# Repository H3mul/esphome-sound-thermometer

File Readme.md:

# Sound Thermometer

A quick ESPHome project that illuminates an addressable LED strip based on sound levels detected by a microphone module.

## Features

- Custom LED effect that lerps between two colors based on sound level
- Configurable sound sensitivity and LED colors via ESPHome webui
- Support for USB C and A power source capability detection
- Safety kill switch via a mosfet to disable the LED load if the power source doesn't support enough current
- Pins for power switch

## Media

https://github.com/user-attachments/assets/a23c17ae-ab65-41b6-94d6-0d3440485dc3

## Hardware Design

### Schematic Diagram

### PCB Layout

## Components

- Microcontroller (ESP32-C3 Super Mini)
- WS2812B LED strip
- Microphone module with analog out (e.g., MAX9814)
- AMS1117-3.3 Voltage Regulator for clean mic module power
- P-Channel MOSFET for power control (AO3401)
- P2N2222A NPN transistor for mosfet driving
- USB C 8-pin breakout board with 5.1k resistors for CC pins (designating the device as a power drain)
- Bulk and filter capacitors
- A few resistors (see schematic for details)

## ESPHome Installation & Configuration

### Prerequisites

- ESPHome installed on your system
- Home Assistant instance (optional, for integration)
- A compatible microcontroller (as defined in your configuration)
- USB cable for flashing

### Setup Instructions

1. **Clone or download this configuration:**
   ```bash
   git clone https://github.com/H3mul/esphome-sound-thermometer.git
   ```

2. **Create or update your ESPHome configuration file:**
   - Use the provided [`esphome/sound-thermometer-config.yaml`](esphome/sound-thermometer-config.yaml) file in this directory
   - Adjust any pins, WiFi credentials, or device settings as needed
   - Add your own `secrets.yaml` with sensitive information referenced in the config

3. **Flash the device:**
   ```bash
   esphome run esphome/sound-thermometer-config.yaml
   ```

4. **Access the webui:**
   - Once flashed, the device will either connect to your WiFi or create an access point
   - Connect to the same network as the device and access the ESPHome dashboard via the device's IP

## Support & Documentation

For more information about ESPHome configuration, visit:
- [ESPHome Official Documentation](https://esphome.io/)

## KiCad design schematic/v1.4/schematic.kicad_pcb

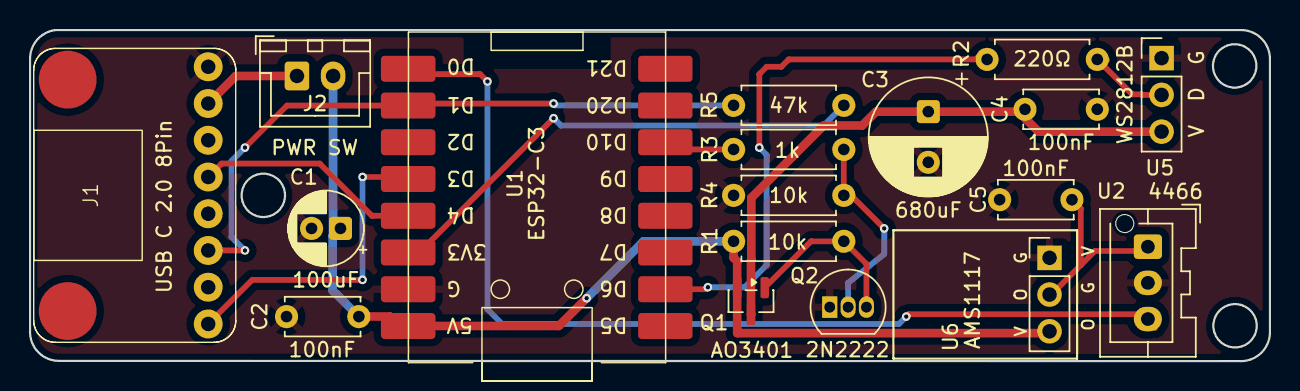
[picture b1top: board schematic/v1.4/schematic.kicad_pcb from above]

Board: 4 copper layers, 85.7 x 22.9 mm, 18 parts (0 on the bottom side), 15 nets.

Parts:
C1: 100uF; CP_Radial_D5.0mm_P2.00mm
C2, C4, C5: 100nF; C_Disc_D5.0mm_W2.5mm_P5.00mm
C3: 680uF; CP_Radial_D8.0mm_P3.50mm
J1: USB C 2.0 8Pin; USB_C_8Pin_Breakout
J2: PWR SW; JST_XH_B2B-XH-A_1x02_P2.50mm_Vertical
Q1: AO3401; SOT-23
Q2: 2N2222; TO-92_Inline
R1, R4: 10k; R_Axial_DIN0207_L6.3mm_D2.5mm_P7.62mm_Horizontal
R2: 220Ω; R_Axial_DIN0207_L6.3mm_D2.5mm_P7.62mm_Horizontal
R3: 1k; R_Axial_DIN0207_L6.3mm_D2.5mm_P7.62mm_Horizontal
R5: 47k; R_Axial_DIN0207_L6.3mm_D2.5mm_P7.62mm_Horizontal
U1: ESP32-C3; ESP32-C3 Super Mini
U2: 4466; JST_XA_B03B-XASK-1-A_1x03_P2.50mm_Vertical
U5: WS2812B; PinHeader_1x03_P2.54mm_Vertical
U6: AMS1117; PinHeader_1x03_P2.54mm_Vertical

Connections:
+3.3V: R5.2, U1.3 (3V3)
+5V: C1.1, C2.1, J2.2, Q1.2 (S), R1.1, U1.1 (5V), U6.3 (VI)
+5VD: C3.1, C4.2, Q1.3 (D), U5.3 (VDD)
CC1: J1.A5 (CC1), U1.4 (D4)
CC2: J1.B5 (CC2), U1.5 (D3)
D+: J1.A6 (D+), R5.1, U1.7 (D1)
GND: C1.2, C2.2, C3.2, C4.1, C5.2, J1.A1 (GND), Q2.1 (E), R4.2, U1.2 (GND), U2.2 (GND), U5.1 (GND), U6.1 (ADJ)
LED D: R2.1, U1.10 (D6)
LED SW: R3.1, U1.14 (D10)
MIC: U1.8 (D0), U2.3 (OUT)
unnamed: J1.A4 (VBUS), J2.1
unnamed: Q1.1 (G), Q2.3 (C), R1.2
unnamed: Q2.2 (B), R3.2, R4.1
unnamed: C5.1, U2.1 (VCC), U6.2 (VO)
unnamed: R2.2, U5.2 (DIN)

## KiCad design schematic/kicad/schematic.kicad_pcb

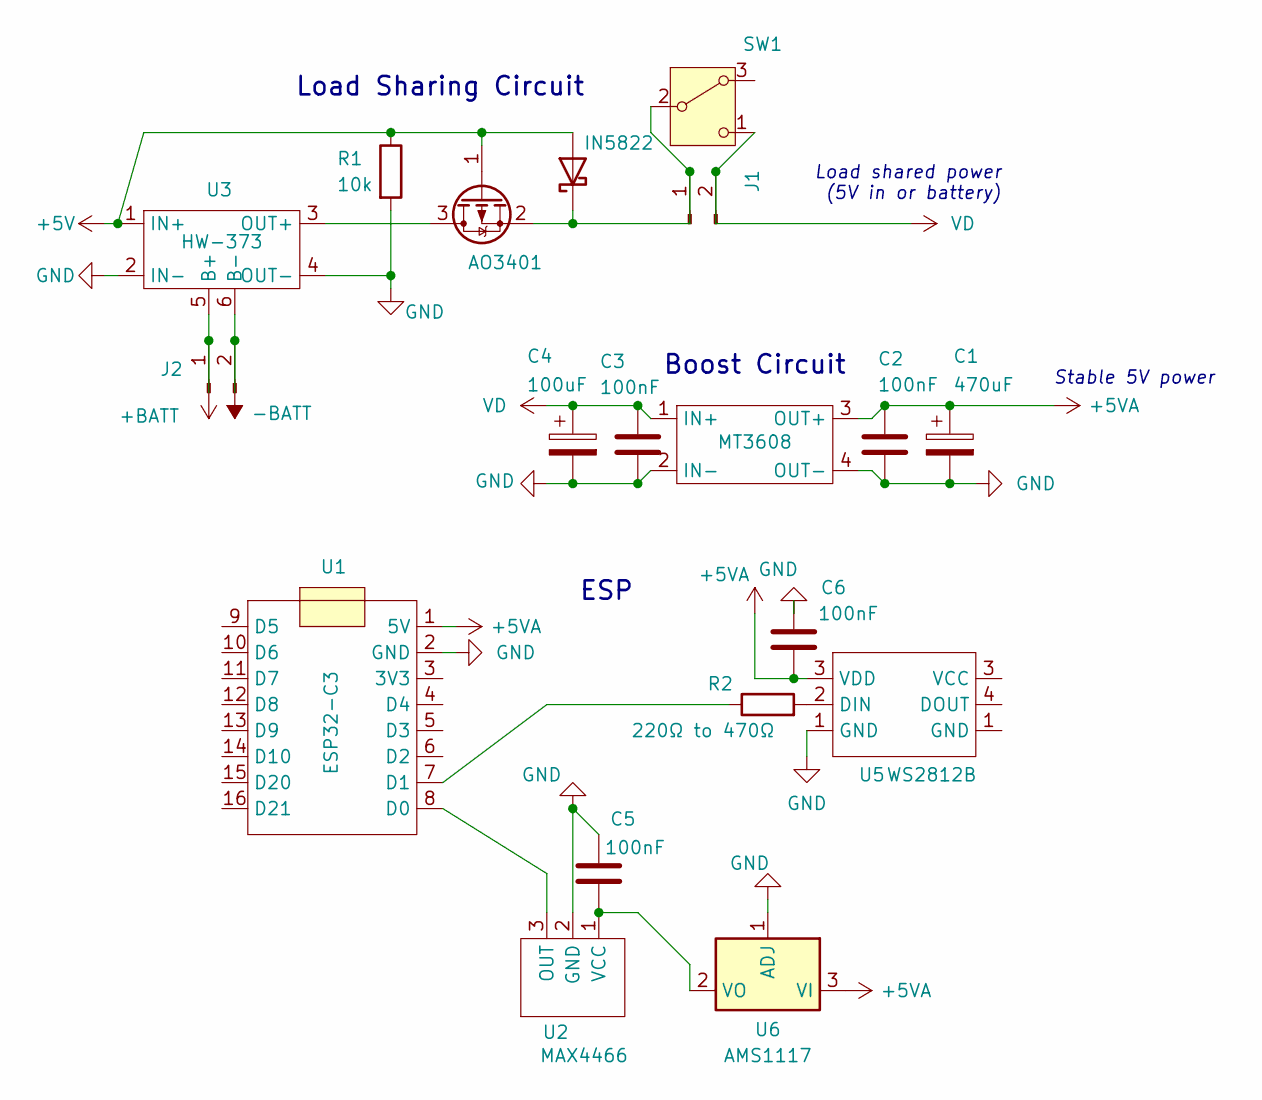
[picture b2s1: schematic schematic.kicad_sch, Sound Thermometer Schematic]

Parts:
C1: 470uF; CP_Radial_D5.0mm_P2.50mm
C2, C3, C5, C6: 100nF; C_Disc_D5.0mm_W2.5mm_P5.00mm
C4: 100uF; CP_Radial_D6.3mm_P2.50mm
IN5822: D_Schottky; D_DO-27_P12.70mm_Horizontal
J1, J2: Conn_01x02_Pin; JST_XA_B02B-XASK-1_1x02_P2.50mm_Vertical
Q1: AO3401; SOT-23
R1: 10k; R_Axial_DIN0207_L6.3mm_D2.5mm_P7.62mm_Horizontal
R2: 220Ω to 470Ω; R_Axial_DIN0207_L6.3mm_D2.5mm_P7.62mm_Horizontal
SW1: SW_Nidec_CAS-120A1; JST_XH_B2B-XH-A_1x02_P2.50mm_Vertical
U1: ESP32-C3; ESP32-C3 Super Mini
U2: MAX4466; JST_XA_B03B-XASK-1-A_1x03_P2.50mm_Vertical
U3: HW-373; HW-373 Charge Controller
U4: MT3608; MT3608_Voltage_Booster
U5: WS2812B; PinHeader_1x03_P2.54mm_Vertical
U6: AMS1117; PinHeader_1x03_P2.54mm_Vertical

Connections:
+5V: IN5822.2 (A), Q1.1 (G), R1.1, U3.1 (IN+)
+5VA: C1.1, C2.1, C6.1, U1.1 (5V), U4.3 (OUT+), U5.3 (VDD), U6.3 (VI)
+BATT: J2.1, U3.5 (B+)
-BATT: J2.2, U3.6 (B-)
GND: C1.2, C2.2, C3.2, C4.2, C5.2, C6.2, R1.2, U1.2 (GND), U2.2 (GND), U3.2 (IN-), U3.4 (OUT-), U4.2 (IN-), U4.4 (OUT-), U5.1 (GND), U6.1 (ADJ)
unnamed: IN5822.1 (K), J1.1, Q1.2 (S), SW1.2 (B)
unnamed: Q1.3 (D), U3.3 (OUT+)
unnamed: U1.8 (D0), U2.3 (OUT)
unnamed: R2.1, U1.7 (D1)
unnamed: C5.1, U2.1 (VCC), U6.2 (VO)
unnamed: R2.2, U5.2 (DIN)
VD: C3.1, C4.1, J1.2, SW1.1 (C), U4.1 (IN+)

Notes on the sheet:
ESP
(5V in or battery)
Load shared power
Boost Circuit
Stable 5V power
Load Sharing Circuit

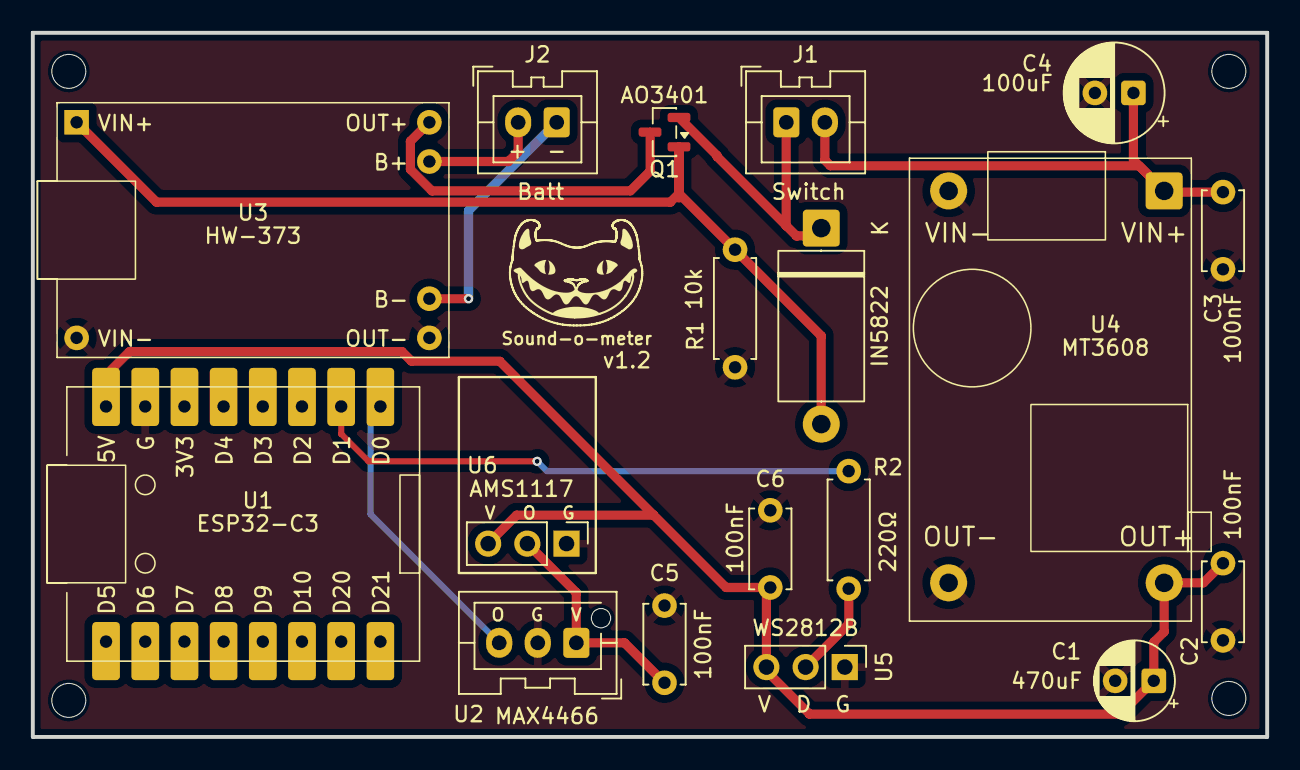
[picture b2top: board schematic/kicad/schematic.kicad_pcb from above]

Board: 4 copper layers, 80.0 x 45.6 mm, 18 parts (0 on the bottom side), 12 nets.

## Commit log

2025-11-09 Add schematic
2025-11-11 Commit esphome
2025-11-14 Add new kicad schematic
2025-11-17 Add gerbers
2025-11-17 Move fakelight into separate repo
2025-11-17 Finalize lights, ready for mic input
2025-11-18 Operational sound meter
2025-11-18 Adjust pcb and schematic
2025-11-18 Add extra signal resistor, update schematic and pcb
2025-11-19 Render + save updated pcb
2025-11-19 Fix issues with pcb for JLCPCB
2025-11-19 Update schematic svg
2025-11-19 Add battery sense circuit
2025-11-20 Add v1.4 usb c version
2025-11-21 Add support for usb c and a power communication with cutoff
2025-11-21 Add usb a power support
2025-11-21 Add D+ pull up
2025-11-21 Adjust power safety
2025-11-21 Adjust sound processing and webui
2025-11-21 Adjust pcb and add icons to webserver
2025-11-23 Final tweaks to pcb
2025-11-24 Add pcb svg and updates
2025-11-24 Final touches before order
2025-11-28 formatting
2025-12-06 Add ota, ap and other tweaks
2025-12-07 Resume using wifi
2025-12-07 Add multiple floors with a switcher, and set AP timeout to 15s
2025-12-07 Add docs
2025-12-07 Update pcb drawing
2025-12-07 Update doc
2025-12-07 Add webui image
2025-12-07 Add video
2025-12-07 Adjust docs
